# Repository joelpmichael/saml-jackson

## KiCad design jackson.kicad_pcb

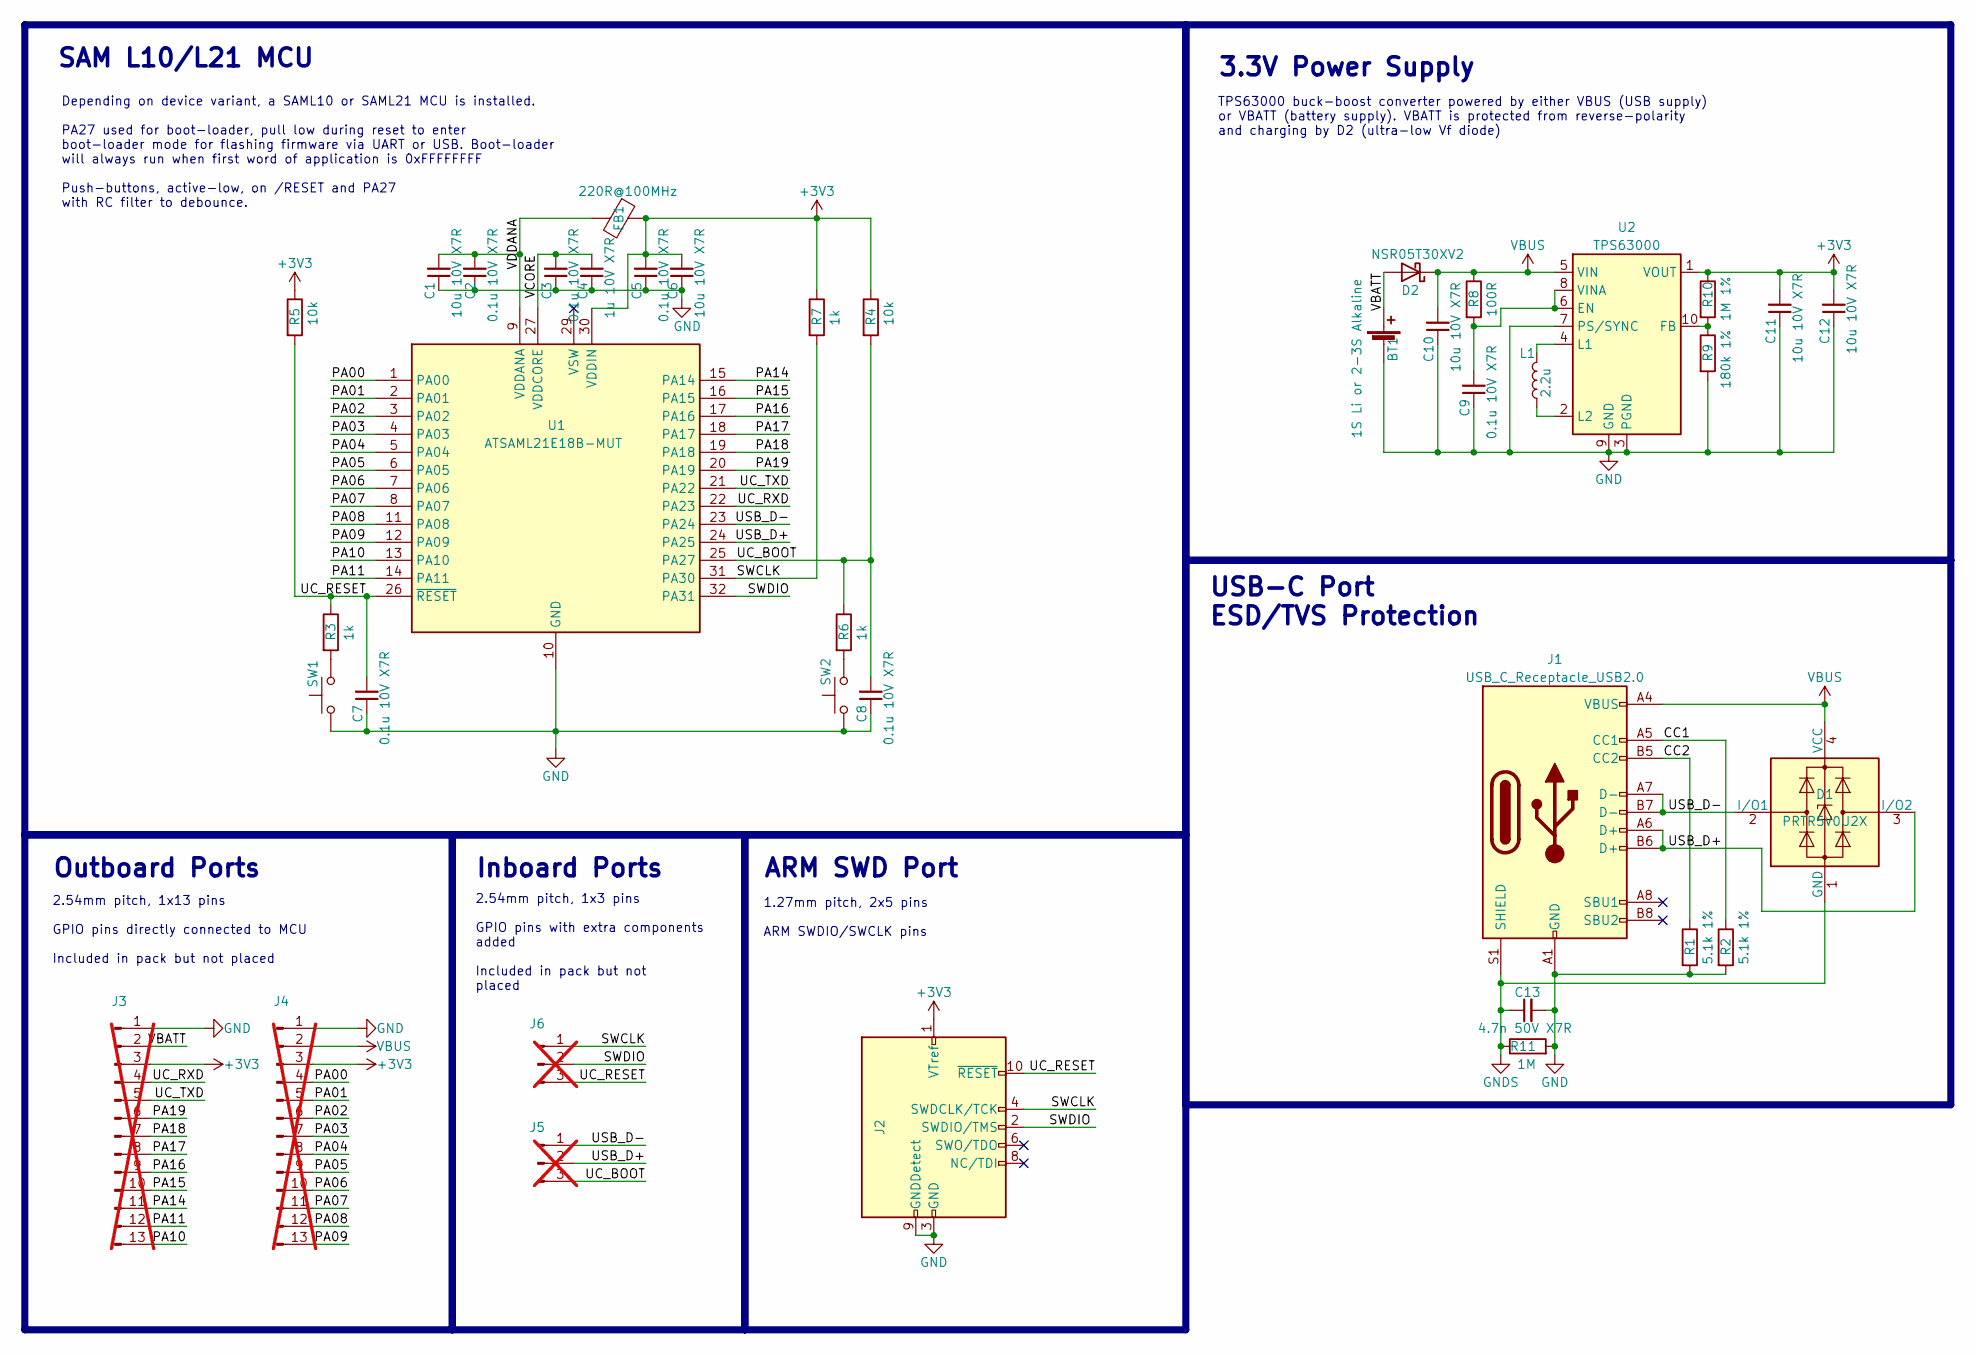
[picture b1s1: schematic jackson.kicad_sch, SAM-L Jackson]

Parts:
BT1: 1S Li or 2-3S Alkaline
C1, C6, C10, C11, C12: 10u 10V X7R; C_0603_1608Metric
C2, C3, C5, C7, C8, C9: 0.1u 10V X7R; C_0402_1005Metric
C4: 1u 10V X7R; C_0402_1005Metric
C13: 4.7n 50V X7R; C_0402_1005Metric
D1: PRTR5V0U2X; SOT-143
D2: NSR05T30XV2; D_SOD-523
FB1: 220R@100MHz; L_0603_1608Metric
J1: USB_C_Receptacle_USB2.0; USB_C_Receptacle_G-Switch_GT-USB-7010ASV
J2: Conn_ARM_JTAG_SWD_10; PinHeader_2x05_P1.27mm_Vertical_SMD
J3, J4: Conn_01x13_Pin; PinHeader_1x13_P2.54mm_Vertical; not fitted
J5, J6: Conn_01x03_Pin; PinHeader_1x03_P2.54mm_Vertical; not fitted
L1: 2.2u; L_1008_2520Metric
R1, R2: 5.1k 1%; R_0402_1005Metric
R3, R6, R7: 1k; R_0402_1005Metric
R4, R5: 10k; R_0402_1005Metric
R8: 100R; R_0402_1005Metric
R9: 180k 1%; R_0402_1005Metric
R10: 1M 1%; R_0402_1005Metric
R11: 1M; R_0402_1005Metric
SW1: RESET; SW_Push_SPST_NO_Alps_SKRK
SW2: BOOT; SW_Push_SPST_NO_Alps_SKRK
U1: ATSAML21E18B-MUT; QFN-32-1EP_5x5mm_P0.5mm_EP3.45x3.45mm
U2: TPS63000; Texas_DRC0010J_ThermalVias

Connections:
+3V3: C5.2, C6.2, C11.2, C12.2, FB1.1, J2.1 (VTref), J3.3, J4.3, R4.1, R5.1, R7.1, R10.1, U1.30 (VDDIN), U2.1 (VOUT)
/CC1: J1.A5 (CC1), R2.1
/CC2: J1.B5 (CC2), R1.1
/PA00: J4.4, U1.1 (PA00)
/PA01: J4.5, U1.2 (PA01)
/PA02: J4.6, U1.3 (PA02)
/PA03: J4.7, U1.4 (PA03)
/PA04: J4.8, U1.5 (PA04)
/PA05: J4.9, U1.6 (PA05)
/PA06: J4.10, U1.7 (PA06)
/PA07: J4.11, U1.8 (PA07)
/PA08: J4.12, U1.11 (PA08)
/PA09: J4.13, U1.12 (PA09)
/PA10: J3.13, U1.13 (PA10)
/PA11: J3.12, U1.14 (PA11)
/PA14: J3.11, U1.15 (PA14)
/PA15: J3.10, U1.16 (PA15)
/PA16: J3.9, U1.17 (PA16)
/PA17: J3.8, U1.18 (PA17)
/PA18: J3.7, U1.19 (PA18)
/PA19: J3.6, U1.20 (PA19)
/SWCLK: J2.4 (SWDCLK/TCK), J6.1, R7.2, U1.31 (PA30)
/SWDIO: J2.2 (SWDIO/TMS), J6.2, U1.32 (PA31)
/UC_BOOT: C8.2, J5.3, R4.2, R6.1, U1.25 (PA27)
/UC_RESET: C7.2, J2.10 (~RESET), J6.3, R3.1, R5.2, U1.26 (~RESET)
/UC_RXD: J3.4, U1.22 (PA23)
/UC_TXD: J3.5, U1.21 (PA22)
/USB_D+: D1.3 (I/O2), J1.A6 (D+), J1.B6 (D+), J5.2, U1.24 (PA25)
/USB_D-: D1.2 (I/O1), J1.A7 (D-), J1.B7 (D-), J5.1, U1.23 (PA24)
/VBATT: BT1.1 (+), D2.2 (A), J3.2
/VCORE: C3.2, C4.2, U1.27 (VDDCORE)
/VDDANA: C1.2, C2.2, FB1.2, U1.9 (VDDANA)
GND: BT1.2 (-), C1.1, C2.1, C3.1, C4.1, C5.1, C6.1, C7.1, C8.1, C9.1, C10.1, C11.1, C12.1, C13.2, J1.A1 (GND), J1.A12 (GND), J1.B1 (GND), J1.B12 (GND), J2.3 (GND), J2.5 (GND), J2.9 (GNDDetect), J3.1, J4.1, R1.2, R2.2, R9.2, R11.2, SW1.1, SW2.2, U1.10 (GND), U1.28 (GND), U2.3 (PGND), U2.7 (PS/SYNC), U2.9 (GND), U2.11 (PGND)
GNDS: C13.1, D1.1 (GND), J1.S1 (SHIELD), R11.1
unnamed: R3.2, SW1.2
unnamed: R6.2, SW2.1
unnamed: C9.2, R8.2, U2.6 (EN), U2.8 (VINA)
unnamed: R9.1, R10.2, U2.10 (FB)
unnamed: L1.2, U2.4 (L1)
unnamed: L1.1, U2.2 (L2)
VBUS: C10.2, D1.4 (VCC), D2.1 (K), J1.A4 (VBUS), J1.A9 (VBUS), J1.B4 (VBUS), J1.B9 (VBUS), J4.2, R8.1, U2.5 (VIN)

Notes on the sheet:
USB-C Port ESD/TVS Protection
1.27mm pitch, 2x5 pins ARM SWDIO/SWCLK pins
SAM L10/L21 MCU
TPS63000 buck-boost converter powered by either VBUS (USB supply) or VBATT (battery supply). VBATT is protected from reverse-polarity and charging by D2 (ultra-low Vf diode)
Outboard Ports
2.54mm pitch, 1x13 pins GPIO pins directly connected to MCU Included in pack but not placed
ARM SWD Port
3.3V Power Supply
2.54mm pitch, 1x3 pins GPIO pins with extra components added Included in pack but not placed
Depending on device variant, a SAML10 or SAML21 MCU is installed. PA27 used for boot-loader, pull low during reset to enter boot-loader mode for flashing firmware via UART or USB. Boot-loader will always run when first word of application is 0xFFFFFFFF Push-buttons, active-low, on /RESET and PA27 w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
Inboard Ports

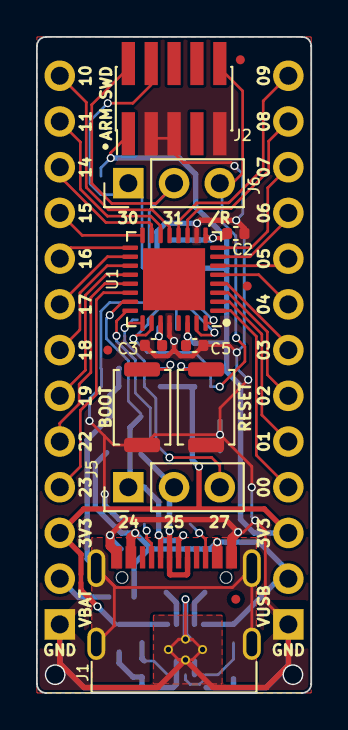
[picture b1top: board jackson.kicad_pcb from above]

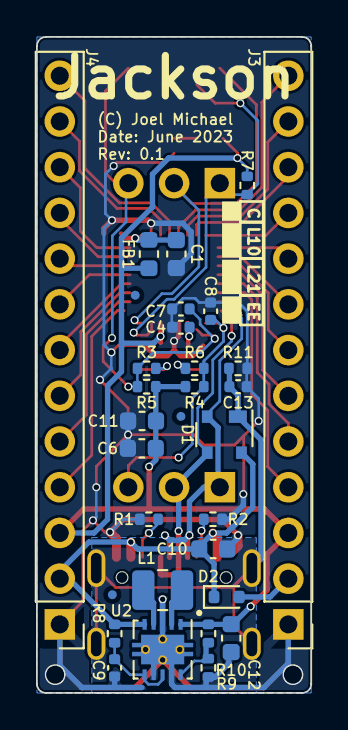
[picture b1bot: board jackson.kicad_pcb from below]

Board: 2 copper layers, 15.2 x 36.4 mm, 38 parts (28 on the bottom side), 41 nets.

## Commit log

2023-06-20 update schematic, add pinout diagram for L10 variant
2023-06-20 SAML21 variant pinout diagram
2023-06-22 Update schematic to use background colour instead of transparent
2023-06-22 Create UUID for the project, used to generate UUIDs for completed boards
2023-06-22 add KiCad schematic and layout
